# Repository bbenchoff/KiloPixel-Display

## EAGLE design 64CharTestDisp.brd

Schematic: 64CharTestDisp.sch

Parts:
D1, D3, D4, D5, D6, D7, D8, D9: 1N4148; SOD-323F
HT16K2, HT16K3, HT16K4, HT16K5, HT16K6, HT16K7, HT16K8, HT16K33: HT16K33_SOP28_SKINNY; SOP28_300MIL_SKINNY
J1: CONN_04JST-PTH-VERT; JST-4-PTH-VERT
J2: CONN_023.5MM; SCREWTERMINAL-3.5MM-2
R6, R7, R11, R12, R16, R17, R18, R19, R26, R27, R31, R32, R36, R37, R41, R42: 10K; 0805-NO
R8, R9, R10, R13, R14, R15, R20, R21, R22, R23, R24, R25, R28, R29, R30, R33, R34, R35, R38, R39, R40, R43, R44, R45: 47K; 0805-NO
U$2, U$3, U$4, U$5, U$11, U$12, U$13, U$14, U$15, U$16, U$17, U$18, U$19, U$20, U$21, U$22, U$23, U$24, U$25, U$26, U$27, U$28, U$29, U$30, U$31, U$32, U$33, U$34, U$37, U$38, U$39, U$40: BIG14SEG; HDSP
U$35, U$36, U$41, U$42: KEYSTONESTANDOFF

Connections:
1A0: HT16K33.P$23 (ROW2/A0), U$2.9 (C), U$3.9 (C), U$4.9 (C), U$5.9 (C)
1A1: HT16K33.P$24 (ROW1/A1), U$2.10 (B), U$3.10 (B), U$4.10 (B), U$5.10 (B)
1A2: HT16K33.P$25 (ROW0/A2), U$2.12 (A), U$3.12 (A), U$4.12 (A), U$5.12 (A)
2A0: HT16K2.P$23 (ROW2/A0), R9.2, U$11.9 (C), U$12.9 (C), U$13.9 (C), U$14.9 (C)
2A1: HT16K2.P$24 (ROW1/A1), U$11.10 (B), U$12.10 (B), U$13.10 (B), U$14.10 (B)
2A2: HT16K2.P$25 (ROW0/A2), U$11.12 (A), U$12.12 (A), U$13.12 (A), U$14.12 (A)
3A0: HT16K3.P$23 (ROW2/A0), U$15.9 (C), U$16.9 (C), U$17.9 (C), U$18.9 (C)
3A1: HT16K3.P$24 (ROW1/A1), R13.2, U$15.10 (B), U$16.10 (B), U$17.10 (B), U$18.10 (B)
3A2: HT16K3.P$25 (ROW0/A2), U$15.12 (A), U$16.12 (A), U$17.12 (A), U$18.12 (A)
4A0: HT16K4.P$23 (ROW2/A0), R24.2, U$19.9 (C), U$20.9 (C), U$21.9 (C), U$22.9 (C)
4A1: HT16K4.P$24 (ROW1/A1), R23.2, U$19.10 (B), U$20.10 (B), U$21.10 (B), U$22.10 (B)
4A2: HT16K4.P$25 (ROW0/A2), U$19.12 (A), U$20.12 (A), U$21.12 (A), U$22.12 (A)
5A0: HT16K5.P$23 (ROW2/A0), U$23.9 (C), U$24.9 (C), U$25.9 (C), U$26.9 (C)
5A1: HT16K5.P$24 (ROW1/A1), U$23.10 (B), U$24.10 (B), U$25.10 (B), U$26.10 (B)
5A2: HT16K5.P$25 (ROW0/A2), R30.2, U$23.12 (A), U$24.12 (A), U$25.12 (A), U$26.12 (A)
6A0: HT16K6.P$23 (ROW2/A0), R34.2, U$27.9 (C), U$28.9 (C), U$29.9 (C), U$30.9 (C)
6A1: HT16K6.P$24 (ROW1/A1), U$27.10 (B), U$28.10 (B), U$29.10 (B), U$30.10 (B)
6A2: HT16K6.P$25 (ROW0/A2), R35.2, U$27.12 (A), U$28.12 (A), U$29.12 (A), U$30.12 (A)
7A0: HT16K7.P$23 (ROW2/A0), U$31.9 (C), U$32.9 (C), U$33.9 (C), U$34.9 (C)
7A1: HT16K7.P$24 (ROW1/A1), R38.2, U$31.10 (B), U$32.10 (B), U$33.10 (B), U$34.10 (B)
7A2: HT16K7.P$25 (ROW0/A2), R40.2, U$31.12 (A), U$32.12 (A), U$33.12 (A), U$34.12 (A)
8A0: HT16K8.P$23 (ROW2/A0), R44.2, U$37.9 (C), U$38.9 (C), U$39.9 (C), U$40.9 (C)
8A1: HT16K8.P$24 (ROW1/A1), R43.2, U$37.10 (B), U$38.10 (B), U$39.10 (B), U$40.10 (B)
8A2: HT16K8.P$25 (ROW0/A2), R45.2, U$37.12 (A), U$38.12 (A), U$39.12 (A), U$40.12 (A)
GND: HT16K2.P$1 (VSS), HT16K3.P$1 (VSS), HT16K4.P$1 (VSS), HT16K5.P$1 (VSS), HT16K6.P$1 (VSS), HT16K7.P$1 (VSS), HT16K8.P$1 (VSS), HT16K33.P$1 (VSS), J1.4, J2.1
unnamed: D1.A, HT16K33.P$2 (COM0/AD), U$2.16 (COM1)
unnamed: D3.A, HT16K2.P$2 (COM0/AD), U$11.16 (COM1)
unnamed: HT16K33.P$22 (ROW3/K1), U$2.7 (D), U$3.7 (D), U$4.7 (D), U$5.7 (D)
unnamed: HT16K33.P$21 (ROW4/K2), U$2.1 (E), U$3.1 (E), U$4.1 (E), U$5.1 (E)
unnamed: HT16K33.P$20 (ROW5/K3), U$2.18 (F), U$3.18 (F), U$4.18 (F), U$5.18 (F)
unnamed: HT16K33.P$19 (ROW6/K4), U$2.13 (N), U$3.13 (N), U$4.13 (N), U$5.13 (N)
unnamed: HT16K33.P$18 (ROW7/K5), U$2.6 (J), U$3.6 (J), U$4.6 (J), U$5.6 (J)
unnamed: D1.C, R20.1, R21.1, R22.1
unnamed: D4.A, HT16K3.P$2 (COM0/AD), U$15.16 (COM1)
unnamed: HT16K33.P$17 (ROW8/K6), U$2.17, U$3.17, U$4.17, U$5.17
unnamed: HT16K33.P$16 (ROW9/K7), U$2.15 (G), U$3.15 (G), U$4.15 (G), U$5.15 (G)
unnamed: HT16K33.P$15 (ROW10/K8), U$2.14 (H), U$3.14 (H), U$4.14 (H), U$5.14 (H)
unnamed: HT16K33.P$4 (COM2/KS1), U$3.16 (COM1)
unnamed: HT16K33.P$8 (COM6), U$5.16 (COM1)
unnamed: HT16K33.P$5 (COM3/KS2), U$3.11 (COM2)
unnamed: HT16K33.P$6 (COM4), U$4.16 (COM1)
unnamed: HT16K33.P$7 (COM5), U$4.11 (COM2)
unnamed: HT16K33.P$9 (COM7), U$5.11 (COM2)
unnamed: D5.A, HT16K4.P$2 (COM0/AD), U$19.16 (COM1)
unnamed: D6.A, HT16K5.P$2 (COM0/AD), U$23.16 (COM1)
unnamed: D7.A, HT16K6.P$2 (COM0/AD), U$27.16 (COM1)
unnamed: D8.A, HT16K7.P$2 (COM0/AD), U$31.16 (COM1)
unnamed: D9.A, HT16K8.P$2 (COM0/AD), U$37.16 (COM1)
unnamed: HT16K33.P$14 (ROW11/K9), U$2.2 (M), U$3.2 (M), U$4.2 (M), U$5.2 (M)
unnamed: HT16K33.P$13 (ROW12/K10), U$2.4 (L), U$3.4 (L), U$4.4 (L), U$5.4 (L)
unnamed: HT16K33.P$12 (ROW13/K11), U$2.5 (K), U$3.5 (K), U$4.5 (K), U$5.5 (K)
unnamed: HT16K33.P$11 (ROW14/K12), U$2.8 (DP), U$3.8 (DP), U$4.8 (DP), U$5.8 (DP)
unnamed: HT16K2.P$22 (ROW3/K1), U$11.7 (D), U$12.7 (D), U$13.7 (D), U$14.7 (D)
unnamed: HT16K2.P$21 (ROW4/K2), U$11.1 (E), U$12.1 (E), U$13.1 (E), U$14.1 (E)
unnamed: HT16K2.P$20 (ROW5/K3), U$11.18 (F), U$12.18 (F), U$13.18 (F), U$14.18 (F)
unnamed: HT16K2.P$19 (ROW6/K4), U$11.13 (N), U$12.13 (N), U$13.13 (N), U$14.13 (N)
unnamed: HT16K2.P$18 (ROW7/K5), U$11.6 (J), U$12.6 (J), U$13.6 (J), U$14.6 (J)
unnamed: D3.C, R8.1, R9.1, R10.1
unnamed: HT16K2.P$17 (ROW8/K6), U$11.17, U$12.17, U$13.17, U$14.17
unnamed: HT16K2.P$16 (ROW9/K7), U$11.15 (G), U$12.15 (G), U$13.15 (G), U$14.15 (G)
unnamed: HT16K2.P$15 (ROW10/K8), U$11.14 (H), U$12.14 (H), U$13.14 (H), U$14.14 (H)
unnamed: HT16K2.P$14 (ROW11/K9), U$11.2 (M), U$12.2 (M), U$13.2 (M), U$14.2 (M)
unnamed: HT16K2.P$13 (ROW12/K10), U$11.4 (L), U$12.4 (L), U$13.4 (L), U$14.4 (L)
unnamed: HT16K2.P$12 (ROW13/K11), U$11.5 (K), U$12.5 (K), U$13.5 (K), U$14.5 (K)
unnamed: HT16K2.P$11 (ROW14/K12), U$11.8 (DP), U$12.8 (DP), U$13.8 (DP), U$14.8 (DP)
unnamed: HT16K2.P$5 (COM3/KS2), U$12.11 (COM2)
unnamed: HT16K2.P$4 (COM2/KS1), U$12.16 (COM1)
unnamed: HT16K2.P$6 (COM4), U$13.16 (COM1)
unnamed: HT16K2.P$7 (COM5), U$13.11 (COM2)
unnamed: HT16K2.P$8 (COM6), U$14.16 (COM1)
unnamed: HT16K2.P$9 (COM7), U$14.11 (COM2)
unnamed: HT16K2.P$3 (COM1/KS0), U$11.11 (COM2)
unnamed: HT16K3.P$22 (ROW3/K1), U$15.7 (D), U$16.7 (D), U$17.7 (D), U$18.7 (D)
unnamed: HT16K3.P$21 (ROW4/K2), U$15.1 (E), U$16.1 (E), U$17.1 (E), U$18.1 (E)
unnamed: HT16K3.P$20 (ROW5/K3), U$15.18 (F), U$16.18 (F), U$17.18 (F), U$18.18 (F)
unnamed: HT16K3.P$19 (ROW6/K4), U$15.13 (N), U$16.13 (N), U$17.13 (N), U$18.13 (N)
unnamed: HT16K3.P$18 (ROW7/K5), U$15.6 (J), U$16.6 (J), U$17.6 (J), U$18.6 (J)
unnamed: D4.C, R13.1, R14.1, R15.1
unnamed: HT16K3.P$17 (ROW8/K6), U$15.17, U$16.17, U$17.17, U$18.17
unnamed: HT16K3.P$16 (ROW9/K7), U$15.15 (G), U$16.15 (G), U$17.15 (G), U$18.15 (G)
unnamed: HT16K3.P$15 (ROW10/K8), U$15.14 (H), U$16.14 (H), U$17.14 (H), U$18.14 (H)
unnamed: HT16K3.P$14 (ROW11/K9), U$15.2 (M), U$16.2 (M), U$17.2 (M), U$18.2 (M)
unnamed: HT16K3.P$13 (ROW12/K10), U$15.4 (L), U$16.4 (L), U$17.4 (L), U$18.4 (L)
unnamed: HT16K3.P$12 (ROW13/K11), U$15.5 (K), U$16.5 (K), U$17.5 (K), U$18.5 (K)
unnamed: HT16K3.P$11 (ROW14/K12), U$15.8 (DP), U$16.8 (DP), U$17.8 (DP), U$18.8 (DP)
unnamed: HT16K3.P$5 (COM3/KS2), U$16.11 (COM2)
unnamed: HT16K3.P$4 (COM2/KS1), U$16.16 (COM1)
unnamed: HT16K3.P$6 (COM4), U$17.16 (COM1)
unnamed: HT16K3.P$7 (COM5), U$17.11 (COM2)
unnamed: HT16K3.P$8 (COM6), U$18.16 (COM1)
unnamed: HT16K3.P$9 (COM7), U$18.11 (COM2)
unnamed: HT16K3.P$3 (COM1/KS0), U$15.11 (COM2)
unnamed: HT16K33.P$3 (COM1/KS0), U$2.11 (COM2)
unnamed: HT16K4.P$22 (ROW3/K1), U$19.7 (D), U$20.7 (D), U$21.7 (D), U$22.7 (D)
unnamed: HT16K4.P$21 (ROW4/K2), U$19.1 (E), U$20.1 (E), U$21.1 (E), U$22.1 (E)
unnamed: HT16K4.P$20 (ROW5/K3), U$19.18 (F), U$20.18 (F), U$21.18 (F), U$22.18 (F)
unnamed: HT16K4.P$19 (ROW6/K4), U$19.13 (N), U$20.13 (N), U$21.13 (N), U$22.13 (N)
unnamed: HT16K4.P$18 (ROW7/K5), U$19.6 (J), U$20.6 (J), U$21.6 (J), U$22.6 (J)
unnamed: D5.C, R23.1, R24.1, R25.1
unnamed: HT16K4.P$17 (ROW8/K6), U$19.17, U$20.17, U$21.17, U$22.17
unnamed: HT16K4.P$16 (ROW9/K7), U$19.15 (G), U$20.15 (G), U$21.15 (G), U$22.15 (G)
unnamed: HT16K4.P$15 (ROW10/K8), U$19.14 (H), U$20.14 (H), U$21.14 (H), U$22.14 (H)
unnamed: HT16K4.P$14 (ROW11/K9), U$19.2 (M), U$20.2 (M), U$21.2 (M), U$22.2 (M)
unnamed: HT16K4.P$13 (ROW12/K10), U$19.4 (L), U$20.4 (L), U$21.4 (L), U$22.4 (L)
unnamed: HT16K4.P$12 (ROW13/K11), U$19.5 (K), U$20.5 (K), U$21.5 (K), U$22.5 (K)
unnamed: HT16K4.P$11 (ROW14/K12), U$19.8 (DP), U$20.8 (DP), U$21.8 (DP), U$22.8 (DP)
unnamed: HT16K4.P$5 (COM3/KS2), U$20.11 (COM2)
unnamed: HT16K4.P$4 (COM2/KS1), U$20.16 (COM1)
unnamed: HT16K4.P$6 (COM4), U$21.16 (COM1)
unnamed: HT16K4.P$7 (COM5), U$21.11 (COM2)
unnamed: HT16K4.P$8 (COM6), U$22.16 (COM1)
unnamed: HT16K4.P$9 (COM7), U$22.11 (COM2)
unnamed: HT16K4.P$3 (COM1/KS0), U$19.11 (COM2)
unnamed: HT16K5.P$22 (ROW3/K1), U$23.7 (D), U$24.7 (D), U$25.7 (D), U$26.7 (D)
unnamed: HT16K5.P$21 (ROW4/K2), U$23.1 (E), U$24.1 (E), U$25.1 (E), U$26.1 (E)
unnamed: HT16K5.P$20 (ROW5/K3), U$23.18 (F), U$24.18 (F), U$25.18 (F), U$26.18 (F)
unnamed: HT16K5.P$19 (ROW6/K4), U$23.13 (N), U$24.13 (N), U$25.13 (N), U$26.13 (N)
unnamed: HT16K5.P$18 (ROW7/K5), U$23.6 (J), U$24.6 (J), U$25.6 (J), U$26.6 (J)
unnamed: D6.C, R28.1, R29.1, R30.1
unnamed: HT16K5.P$17 (ROW8/K6), U$23.17, U$24.17, U$25.17, U$26.17
unnamed: HT16K5.P$16 (ROW9/K7), U$23.15 (G), U$24.15 (G), U$25.15 (G), U$26.15 (G)
unnamed: HT16K5.P$15 (ROW10/K8), U$23.14 (H), U$24.14 (H), U$25.14 (H), U$26.14 (H)
unnamed: HT16K5.P$14 (ROW11/K9), U$23.2 (M), U$24.2 (M), U$25.2 (M), U$26.2 (M)
unnamed: HT16K5.P$13 (ROW12/K10), U$23.4 (L), U$24.4 (L), U$25.4 (L), U$26.4 (L)
unnamed: HT16K5.P$12 (ROW13/K11), U$23.5 (K), U$24.5 (K), U$25.5 (K), U$26.5 (K)
unnamed: HT16K5.P$11 (ROW14/K12), U$23.8 (DP), U$24.8 (DP), U$25.8 (DP), U$26.8 (DP)
unnamed: HT16K5.P$5 (COM3/KS2), U$24.11 (COM2)
unnamed: HT16K5.P$4 (COM2/KS1), U$24.16 (COM1)
unnamed: HT16K5.P$6 (COM4), U$25.16 (COM1)
unnamed: HT16K5.P$7 (COM5), U$25.11 (COM2)
unnamed: HT16K5.P$8 (COM6), U$26.16 (COM1)
unnamed: HT16K5.P$9 (COM7), U$26.11 (COM2)
unnamed: HT16K5.P$3 (COM1/KS0), U$23.11 (COM2)
unnamed: HT16K6.P$22 (ROW3/K1), U$27.7 (D), U$28.7 (D), U$29.7 (D), U$30.7 (D)
unnamed: HT16K6.P$21 (ROW4/K2), U$27.1 (E), U$28.1 (E), U$29.1 (E), U$30.1 (E)
unnamed: HT16K6.P$20 (ROW5/K3), U$27.18 (F), U$28.18 (F), U$29.18 (F), U$30.18 (F)
unnamed: HT16K6.P$19 (ROW6/K4), U$27.13 (N), U$28.13 (N), U$29.13 (N), U$30.13 (N)
unnamed: HT16K6.P$18 (ROW7/K5), U$27.6 (J), U$28.6 (J), U$29.6 (J), U$30.6 (J)
unnamed: D7.C, R33.1, R34.1, R35.1
unnamed: HT16K6.P$17 (ROW8/K6), U$27.17, U$28.17, U$29.17, U$30.17
unnamed: HT16K6.P$16 (ROW9/K7), U$27.15 (G), U$28.15 (G), U$29.15 (G), U$30.15 (G)
unnamed: HT16K6.P$15 (ROW10/K8), U$27.14 (H), U$28.14 (H), U$29.14 (H), U$30.14 (H)
unnamed: HT16K6.P$14 (ROW11/K9), U$27.2 (M), U$28.2 (M), U$29.2 (M), U$30.2 (M)
unnamed: HT16K6.P$13 (ROW12/K10), U$27.4 (L), U$28.4 (L), U$29.4 (L), U$30.4 (L)
unnamed: HT16K6.P$12 (ROW13/K11), U$27.5 (K), U$28.5 (K), U$29.5 (K), U$30.5 (K)
unnamed: HT16K6.P$11 (ROW14/K12), U$27.8 (DP), U$28.8 (DP), U$29.8 (DP), U$30.8 (DP)
unnamed: HT16K6.P$5 (COM3/KS2), U$28.11 (COM2)
unnamed: HT16K6.P$4 (COM2/KS1), U$28.16 (COM1)
unnamed: HT16K6.P$6 (COM4), U$29.16 (COM1)
unnamed: HT16K6.P$7 (COM5), U$29.11 (COM2)
unnamed: HT16K6.P$8 (COM6), U$30.16 (COM1)
unnamed: HT16K6.P$9 (COM7), U$30.11 (COM2)
unnamed: HT16K6.P$3 (COM1/KS0), U$27.11 (COM2)
unnamed: HT16K7.P$22 (ROW3/K1), U$31.7 (D), U$32.7 (D), U$33.7 (D), U$34.7 (D)
unnamed: HT16K7.P$21 (ROW4/K2), U$31.1 (E), U$32.1 (E), U$33.1 (E), U$34.1 (E)
unnamed: HT16K7.P$20 (ROW5/K3), U$31.18 (F), U$32.18 (F), U$33.18 (F), U$34.18 (F)
unnamed: HT16K7.P$19 (ROW6/K4), U$31.13 (N), U$32.13 (N), U$33.13 (N), U$34.13 (N)
unnamed: HT16K7.P$18 (ROW7/K5), U$31.6 (J), U$32.6 (J), U$33.6 (J), U$34.6 (J)
unnamed: D8.C, R38.1, R39.1, R40.1
unnamed: HT16K7.P$17 (ROW8/K6), U$31.17, U$32.17, U$33.17, U$34.17
unnamed: HT16K7.P$16 (ROW9/K7), U$31.15 (G), U$32.15 (G), U$33.15 (G), U$34.15 (G)
unnamed: HT16K7.P$15 (ROW10/K8), U$31.14 (H), U$32.14 (H), U$33.14 (H), U$34.14 (H)
unnamed: HT16K7.P$14 (ROW11/K9), U$31.2 (M), U$32.2 (M), U$33.2 (M), U$34.2 (M)
unnamed: HT16K7.P$13 (ROW12/K10), U$31.4 (L), U$32.4 (L), U$33.4 (L), U$34.4 (L)
unnamed: HT16K7.P$12 (ROW13/K11), U$31.5 (K), U$32.5 (K), U$33.5 (K), U$34.5 (K)
unnamed: HT16K7.P$11 (ROW14/K12), U$31.8 (DP), U$32.8 (DP), U$33.8 (DP), U$34.8 (DP)
unnamed: HT16K7.P$5 (COM3/KS2), U$32.11 (COM2)
unnamed: HT16K7.P$4 (COM2/KS1), U$32.16 (COM1)
unnamed: HT16K7.P$6 (COM4), U$33.16 (COM1)
unnamed: HT16K7.P$7 (COM5), U$33.11 (COM2)
unnamed: HT16K7.P$8 (COM6), U$34.16 (COM1)
unnamed: HT16K7.P$9 (COM7), U$34.11 (COM2)
unnamed: HT16K7.P$3 (COM1/KS0), U$31.11 (COM2)
unnamed: HT16K8.P$22 (ROW3/K1), U$37.7 (D), U$38.7 (D), U$39.7 (D), U$40.7 (D)
unnamed: HT16K8.P$21 (ROW4/K2), U$37.1 (E), U$38.1 (E), U$39.1 (E), U$40.1 (E)
unnamed: HT16K8.P$20 (ROW5/K3), U$37.18 (F), U$38.18 (F), U$39.18 (F), U$40.18 (F)
unnamed: HT16K8.P$19 (ROW6/K4), U$37.13 (N), U$38.13 (N), U$39.13 (N), U$40.13 (N)
unnamed: HT16K8.P$18 (ROW7/K5), U$37.6 (J), U$38.6 (J), U$39.6 (J), U$40.6 (J)
unnamed: D9.C, R43.1, R44.1, R45.1
unnamed: HT16K8.P$17 (ROW8/K6), U$37.17, U$38.17, U$39.17, U$40.17
unnamed: HT16K8.P$16 (ROW9/K7), U$37.15 (G), U$38.15 (G), U$39.15 (G), U$40.15 (G)
unnamed: HT16K8.P$15 (ROW10/K8), U$37.14 (H), U$38.14 (H), U$39.14 (H), U$40.14 (H)
unnamed: HT16K8.P$14 (ROW11/K9), U$37.2 (M), U$38.2 (M), U$39.2 (M), U$40.2 (M)
unnamed: HT16K8.P$13 (ROW12/K10), U$37.4 (L), U$38.4 (L), U$39.4 (L), U$40.4 (L)
unnamed: HT16K8.P$12 (ROW13/K11), U$37.5 (K), U$38.5 (K), U$39.5 (K), U$40.5 (K)
unnamed: HT16K8.P$11 (ROW14/K12), U$37.8 (DP), U$38.8 (DP), U$39.8 (DP), U$40.8 (DP)
unnamed: HT16K8.P$5 (COM3/KS2), U$38.11 (COM2)
unnamed: HT16K8.P$4 (COM2/KS1), U$38.16 (COM1)
unnamed: HT16K8.P$6 (COM4), U$39.16 (COM1)
unnamed: HT16K8.P$7 (COM5), U$39.11 (COM2)
unnamed: HT16K8.P$8 (COM6), U$40.16 (COM1)
unnamed: HT16K8.P$9 (COM7), U$40.11 (COM2)
unnamed: HT16K8.P$3 (COM1/KS0), U$37.11 (COM2)
SCL: HT16K2.P$26 (SCL), HT16K3.P$26 (SCL), HT16K4.P$26 (SCL), HT16K5.P$26 (SCL), HT16K6.P$26 (SCL), HT16K7.P$26 (SCL), HT16K8.P$26 (SCL), HT16K33.P$26 (SCL), J1.3, R6.2, R11.2, R16.2, R18.2, R26.2, R31.2, R36.2, R41.2
SDA: HT16K2.P$27 (SDA), HT16K3.P$27 (SDA), HT16K4.P$27 (SDA), HT16K5.P$27 (SDA), HT16K6.P$27 (SDA), HT16K7.P$27 (SDA), HT16K8.P$27 (SDA), HT16K33.P$27 (SDA), J1.2, R7.2, R12.2, R17.2, R19.2, R27.2, R32.2, R37.2, R42.2
VDD: HT16K2.P$28 (VDD), HT16K3.P$28 (VDD), HT16K4.P$28 (VDD), HT16K5.P$28 (VDD), HT16K6.P$28 (VDD), HT16K7.P$28 (VDD), HT16K8.P$28 (VDD), HT16K33.P$28 (VDD), J1.1, J2.2, R6.1, R7.1, R11.1, R12.1, R16.1, R17.1, R18.1, R19.1, R26.1, R27.1, R31.1, R32.1, R36.1, R37.1, R41.1, R42.1

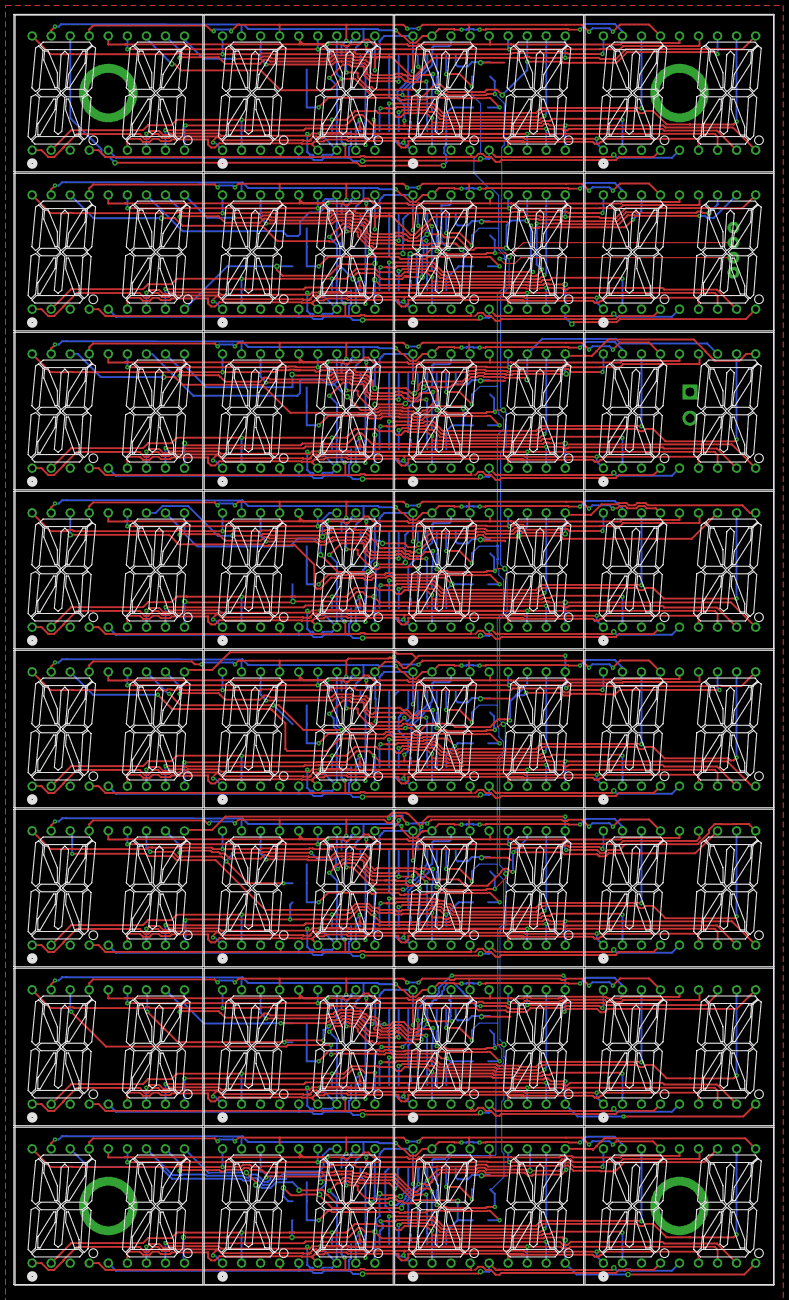
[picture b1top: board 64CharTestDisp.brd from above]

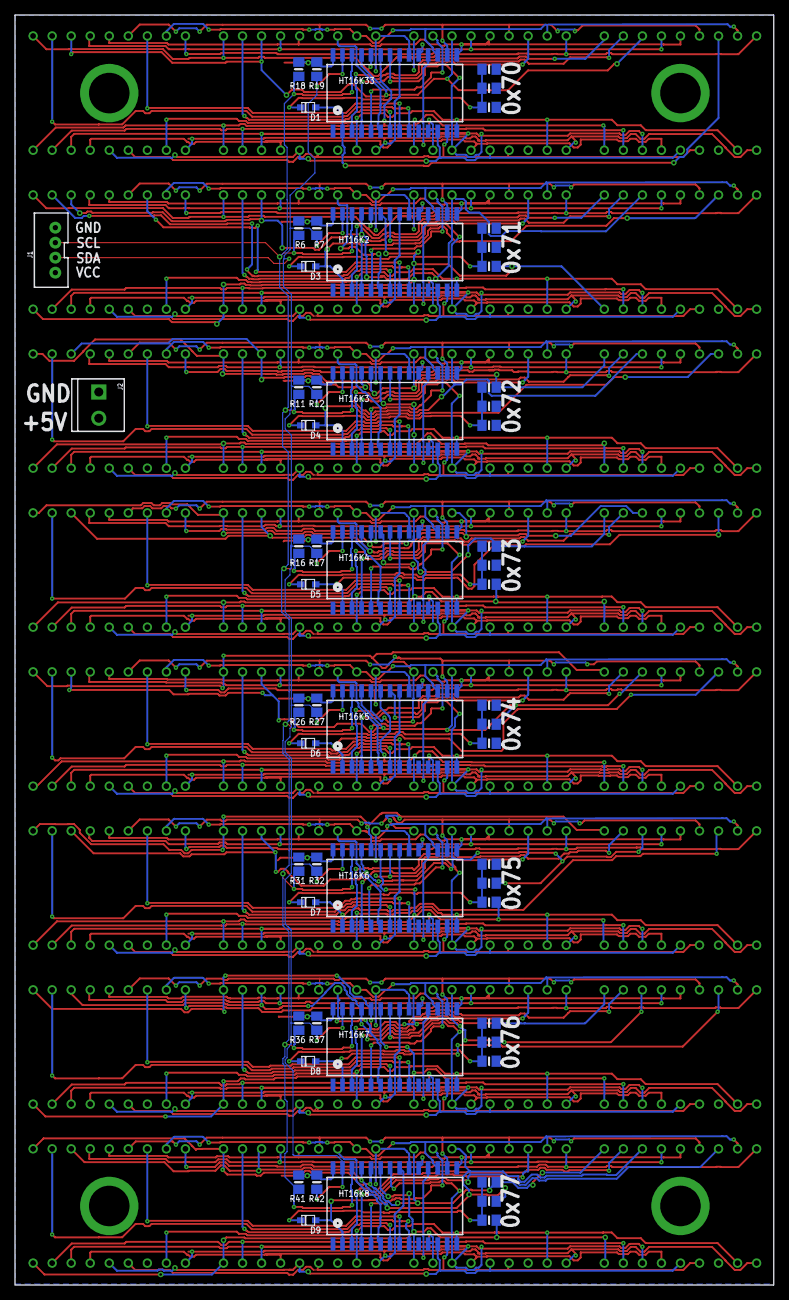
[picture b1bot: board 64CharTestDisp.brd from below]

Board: 2 copper layers, 101.2 x 169.4 mm, 94 parts (58 on the bottom side), 196 nets.

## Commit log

2021-01-15 that might work

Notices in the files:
parts and their libraries:
microbuilder: This work is placed in the public domain, and may be freely used for commercial and non-commercial work with the following conditions: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
SparkFun-Connectors: Licensing: Creative Commons ShareAlike 4.0 International - https://creativecommons.org/licenses/by-sa/4.0
